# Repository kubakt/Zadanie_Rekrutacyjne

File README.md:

# Zadanie_Rekrutacyjne

Wykonałem oba zadania z hardware, korzystałem z programu Autodesk Eagle.
Dałem z siebie tyle ile czas pozwolił :)

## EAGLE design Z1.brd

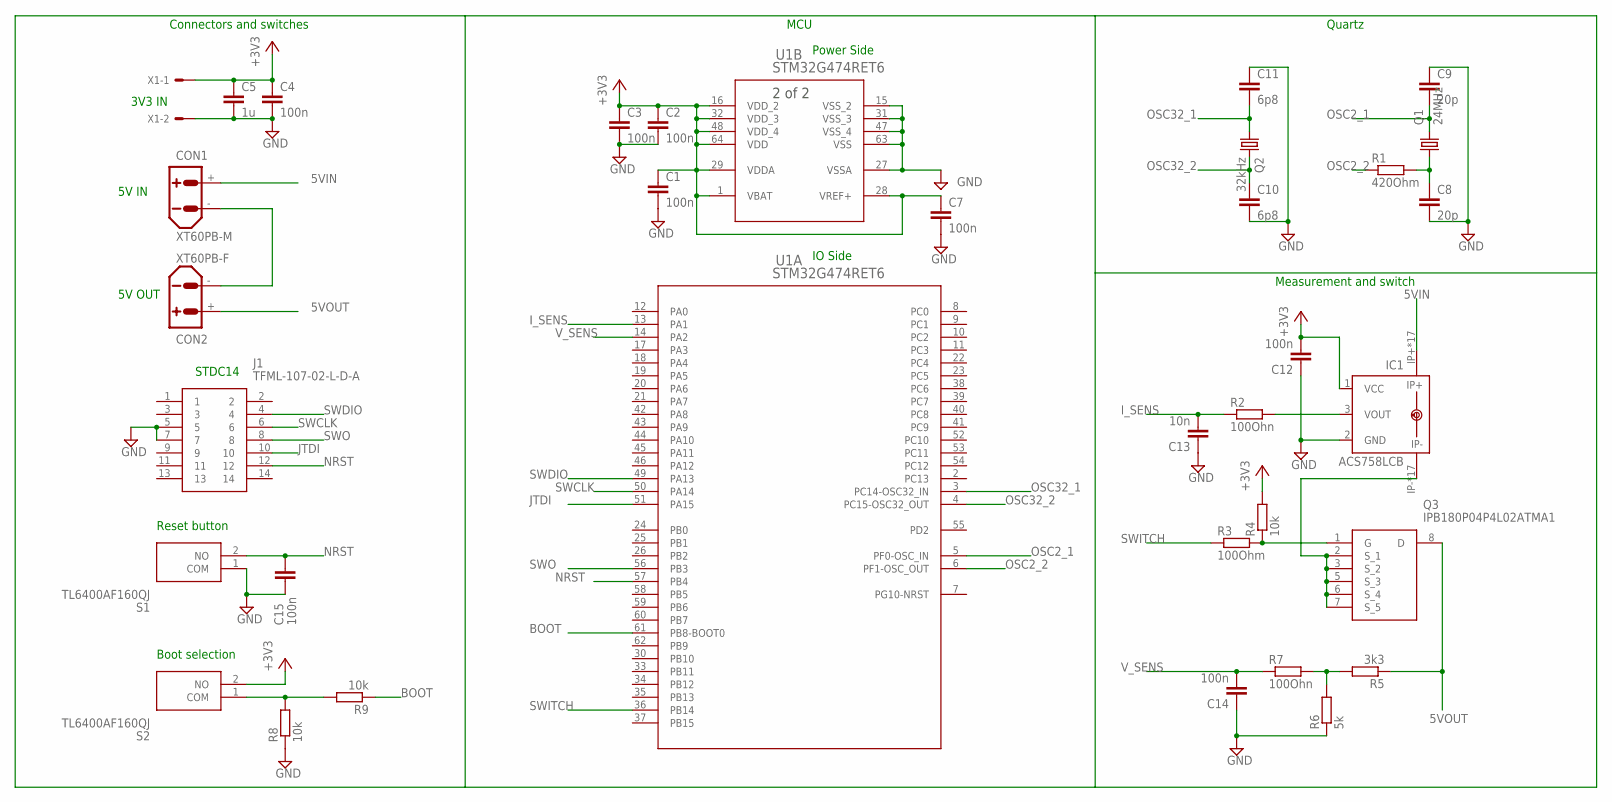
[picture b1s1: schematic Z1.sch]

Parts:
C1, C2, C3, C4, C7, C12, C14, C15: 100n; C0402
C5: 1u; C1206K
C8, C9: 20p; C0402
C10, C11: 6p8; C0402
C13: 10n; C0402
CON1: XT60PB-M
CON2: XT60PB-F
IC1: ACS758LCB; CB-PFF
J1: TFML-107-02-L-D-A; TFML-107-02-XXX-D-A
Q1: 24MHz; 11.4X4.5
Q2: 32kHz; FC-12M
Q3: IPB180P04P4L02ATMA1
R1: 420Ohm; R0603
R2, R7: 100Ohn; R0603
R3: 100Ohm; R0603
R4, R8, R9: 10k; R0603
R5: 3k3; R0603
R6: 5k; R0603
S1, S2: TL6400AF160QJ
U1: STM32G474RET6; LQFP64-10X10MM
X1: KK-156-2

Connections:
5VIN: CON1.+, IC1.IP+, IC1.IP+@2 (IP+), IC1.IP+@3 (IP+), IC1.IP+@4 (IP+), IC1.IP+@5 (IP+), IC1.IP+@6 (IP+), IC1.IP+@7 (IP+), IC1.IP+@8 (IP+), IC1.IP+@9 (IP+), IC1.IP+@10 (IP+), IC1.IP+@11 (IP+), IC1.IP+@12 (IP+), IC1.IP+@13 (IP+), IC1.IP+@14 (IP+), IC1.IP+@15 (IP+), IC1.IP+@16 (IP+), IC1.IP+@17 (IP+)
5VOUT: CON2.+, Q3.8 (D), R5.1
+3V3: C1.1, C2.1, C3.1, C4.1, C5.1, C7.1, C12.2, IC1.1 (VCC), R4.2, S2.2 (NO), U1.1 (VBAT), U1.16 (VDD_2), U1.28 (VREF+), U1.29 (VDDA), U1.32 (VDD_3), U1.48 (VDD_4), U1.64 (VDD), X1.1
AXC: C8.1, Q1.1, R1.2
BOOT: R9.1, U1.61 (PB8-BOOT0)
GND: C1.2, C2.2, C3.2, C4.2, C5.2, C7.2, C8.2, C9.1, C10.2, C11.1, C12.1, C13.1, C14.1, C15.2, IC1.2 (GND), J1.5, J1.7, R6.1, R8.1, S1.1 (COM), U1.15 (VSS_2), U1.27 (VSSA), U1.31 (VSS_3), U1.47 (VSS_4), U1.63 (VSS), X1.2
I_SENS: C13.2, R2.1, U1.13 (PA1)
JTDI: J1.10, U1.51 (PA15)
unnamed: CON1.-, CON2.-
unnamed: IC1.IP-, IC1.IP-@2 (IP-), IC1.IP-@3 (IP-), IC1.IP-@4 (IP-), IC1.IP-@5 (IP-), IC1.IP-@6 (IP-), IC1.IP-@7 (IP-), IC1.IP-@8 (IP-), IC1.IP-@9 (IP-), IC1.IP-@10 (IP-), IC1.IP-@11 (IP-), IC1.IP-@12 (IP-), IC1.IP-@13 (IP-), IC1.IP-@14 (IP-), IC1.IP-@15 (IP-), IC1.IP-@16 (IP-), IC1.IP-@17 (IP-), Q3.2 (S_1), Q3.3 (S_2), Q3.5 (S_3), Q3.6 (S_4), Q3.7 (S_5)
unnamed: IC1.3 (VOUT), R2.2
unnamed: Q3.1 (G), R3.2, R4.1
unnamed: R5.2, R6.2, R7.2
unnamed: R8.2, R9.2, S2.1 (COM)
NRST: C15.1, J1.12, S1.2 (NO), U1.57 (PB4)
OSC2_1: C9.2, Q1.2, U1.5 (PF0-OSC_IN)
OSC2_2: R1.1, U1.6 (PF1-OSC_OUT)
OSC32_1: C11.2, Q2.1, U1.3 (PC14-OSC32_IN)
OSC32_2: C10.1, Q2.2, U1.4 (PC15-OSC32_OUT)
SWCLK: J1.6, U1.50 (PA14)
SWDIO: J1.4, U1.49 (PA13)
SWITCH: R3.1, U1.36 (PB14)
SWO: J1.8, U1.56 (PB3)
V_SENS: C14.2, R7.1, U1.14 (PA2)

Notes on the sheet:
3V3 IN
Power Side
IO Side
5V IN
5V OUT
STDC14
Connectors and switches
MCU
Quartz
Measurement and switch
Reset button
Boot selection

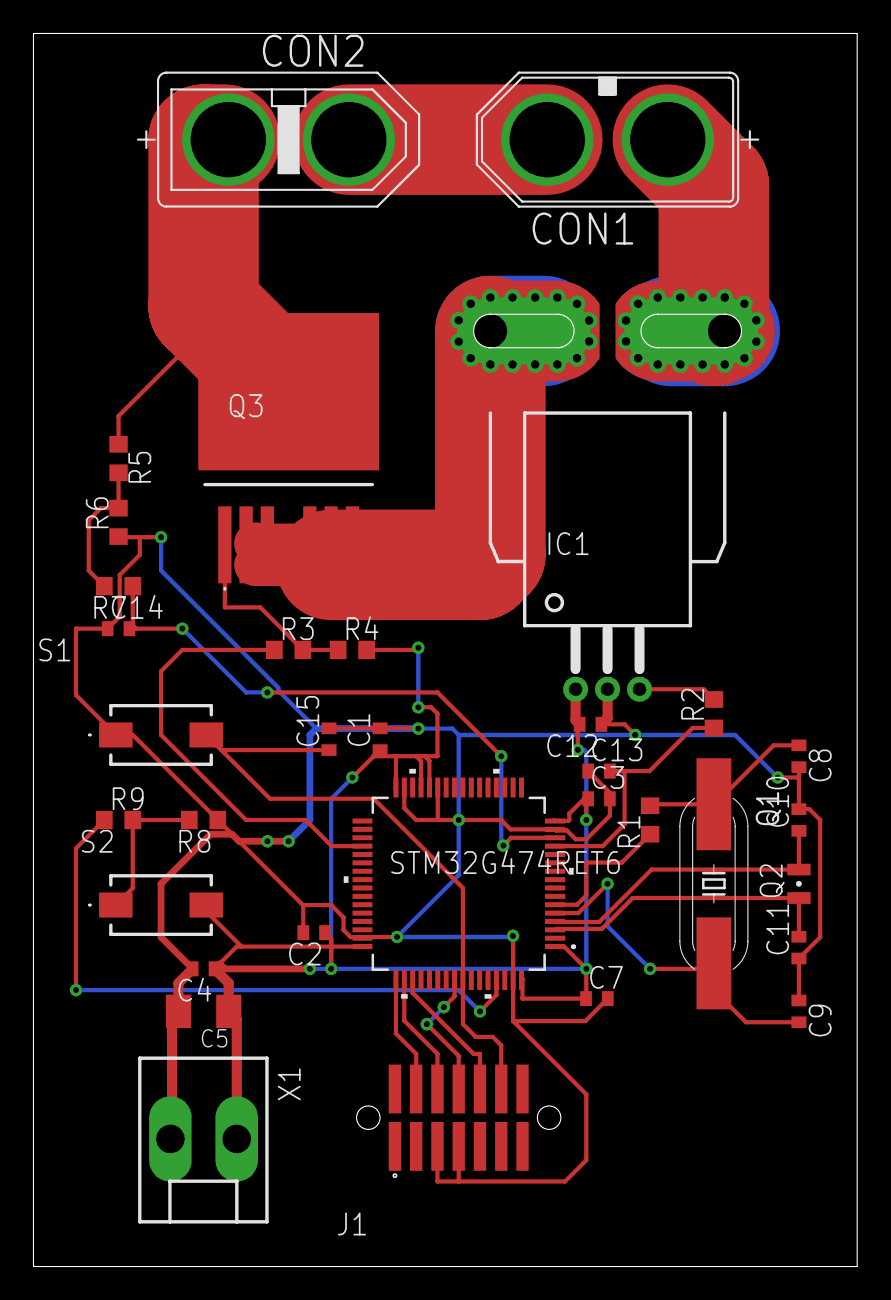
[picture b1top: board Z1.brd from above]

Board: 2 copper layers, 49.2 x 73.7 mm, 34 parts (0 on the bottom side), 24 nets.

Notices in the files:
parts and their libraries:
crystal-geyer_V1_0: Copyright: Geyer-Electronic
COPYRIGHT: Copyright (C) 2022 Ultra Librarian. All rights reserved.
